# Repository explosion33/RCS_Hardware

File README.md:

# RCS_Hardware
SARP 2023 RCS Flight Controller KiCAD project

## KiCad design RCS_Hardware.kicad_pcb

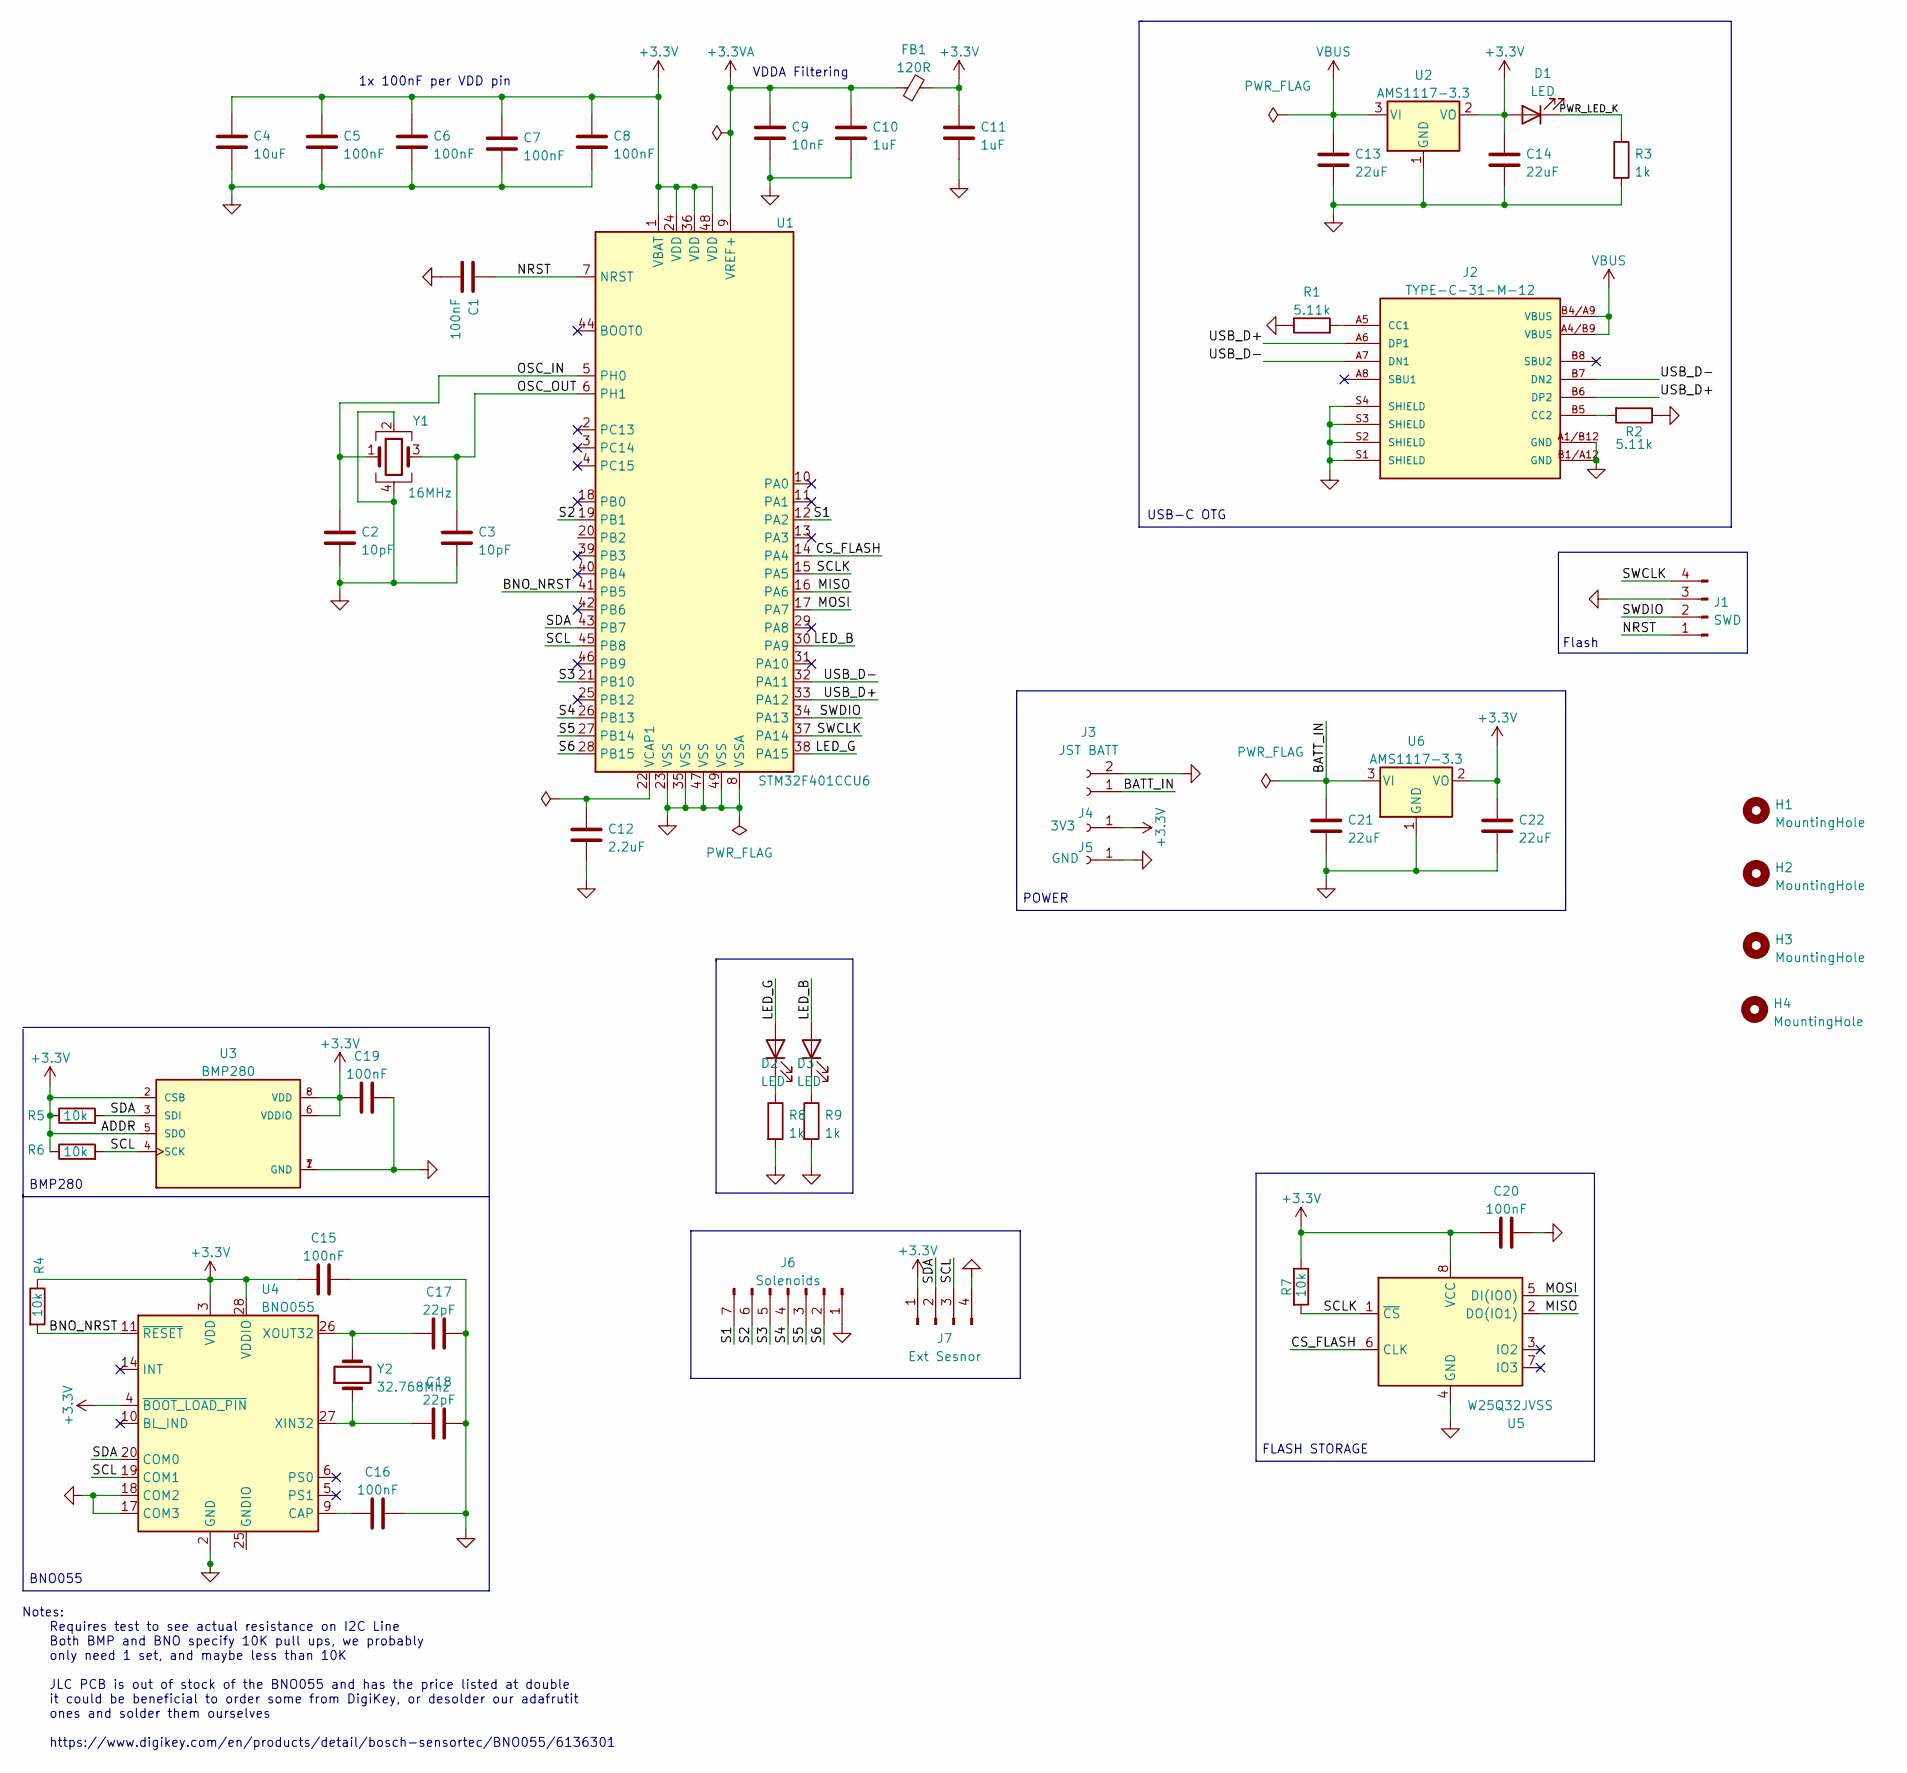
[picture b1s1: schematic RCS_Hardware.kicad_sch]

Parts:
C1, C5, C6, C7, C8, C15, C16, C19, C20: 100nF; C_0402_1005Metric; JLCPCB# C307331
C2, C3: 10pF; C_0402_1005Metric; JLCPCB# C32949
C4: 10uF; C_0603_1608Metric; JLCPCB# C19702
C9: 10nF; C_0402_1005Metric; JLCPCB# C15195
C10, C11: 1uF; C_0402_1005Metric; JLCPCB# C52923
C12: 2.2uF; C_0402_1005Metric; JLCPCB# C12530
C13, C14, C21, C22: 22uF; C_0805_2012Metric; JLCPCB# C5674
C17, C18: 22pF; C_0402_1005Metric; JLCPCB# C466226
D1, D2, D3: LED; LED_0603_1608Metric; JLCPCB# C273598
FB1: 120R; L_0603_1608Metric; JLCPCB# C85831
H1, H2, H3, H4: MountingHole; MountingHole_3.2mm_M3
J1: SWD; PinHeader_1x04_P2.54mm_Vertical
J2: TYPE-C-31-M-12; HRO_TYPE-C-31-M-12; PARTREV 2020.12.08; JLCPCB# C165948
J3: JST BATT; JST_EH_B2B-EH-A_1x02_P2.50mm_Vertical
J4: 3V3; TestPoint_THTPad_2.5x2.5mm_Drill1.2mm
J5: GND; TestPoint_THTPad_2.5x2.5mm_Drill1.2mm
J6: Solenoids; PinHeader_1x07_P2.54mm_Vertical
J7: Ext Sesnor; PinHeader_1x04_P2.54mm_Vertical
R1, R2: 5.11k; R_0402_1005Metric; JLCPCB# C25906
R3, R8, R9: 1k; R_0402_1005Metric; JLCPCB# C11702
R4, R5, R6, R7: 10k; R_0402_1005Metric; JLCPCB# C60490
U1: STM32F401CCU6; QFN-48-1EP_7x7mm_P0.5mm_EP5.6x5.6mm; JLCPCB# C79861
U2, U6: AMS1117-3.3; SOT-223-3_TabPin2; JLCPCB# C6186
U3: BMP280; XDCR_BMP280; PART_REV 1.19; JLCPCB# C83291
U4: BNO055; LGA-28_5.2x3.8mm_P0.5mm; JLCPCB# C93216
U5: W25Q32JVSS; SOIC-8_5.23x5.23mm_P1.27mm; JLCPCB# C82344
Y1: 16MHz; Crystal_SMD_3225-4Pin_3.2x2.5mm; JLCPCB# C13738
Y2: 32.768Mhz; Crystal_SMD_3215-2Pin_3.2x1.5mm; JLCPCB# C907540

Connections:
+3.3V: C4.1, C5.1, C6.1, C7.1, C8.1, C11.1, C14.1, C15.1, C19.2, C20.1, C22.1, D1.2 (A), FB1.2, J4.1, J7.1, R4.1, R5.1, R6.1, R7.1, U1.1 (VBAT), U1.24 (VDD), U1.36 (VDD), U1.48 (VDD), U2.2 (VO), U3.2 (CSB), U3.5 (SDO), U3.6 (VDDIO), U3.8 (VDD), U4.3 (VDD), U4.4 (~BOOT_LOAD_PIN), U4.28 (VDDIO), U5.8 (VCC), U6.2 (VO)
+3.3VA: C9.1, C10.1, FB1.1, U1.9 (VREF+)
/BATT_IN: C21.1, J3.1, U6.3 (VI)
/BNO_NRST: R4.2, U1.41 (PB5), U4.11 (~RESET)
/CS_FLASH: U1.14 (PA4), U5.6 (CLK)
/LED_B: D3.2 (A), U1.30 (PA9)
/LED_G: D2.2 (A), U1.38 (PA15)
/MISO: U1.16 (PA6), U5.2 (DO(IO1))
/MOSI: U1.17 (PA7), U5.5 (DI(IO0))
/NRST: C1.1, J1.1, U1.7 (NRST)
/OSC_IN: C2.1, U1.5 (PH0), Y1.1
/OSC_OUT: C3.1, U1.6 (PH1), Y1.3
/PWR_LED_K: D1.1 (K), R3.1
/S1: J6.7, U1.12 (PA2)
/S2: J6.6, U1.19 (PB1)
/S3: J6.5, U1.21 (PB10)
/S4: J6.4, U1.26 (PB13)
/S5: J6.3, U1.27 (PB14)
/S6: J6.2, U1.28 (PB15)
/SCL: J7.3, R6.2, U1.45 (PB8), U3.4 (SCK), U4.19 (COM1)
/SCLK: R7.2, U1.15 (PA5), U5.1 (~CS)
/SDA: J7.2, R5.2, U1.43 (PB7), U3.3 (SDI), U4.20 (COM0)
/SWCLK: J1.4, U1.37 (PA14)
/SWDIO: J1.2, U1.34 (PA13)
/USB_D+: J2.A6 (DP1), J2.B6 (DP2), U1.33 (PA12)
/USB_D-: J2.A7 (DN1), J2.B7 (DN2), U1.32 (PA11)
GND: C1.2, C2.2, C3.2, C4.2, C5.2, C6.2, C7.2, C8.2, C9.2, C10.2, C11.2, C12.2, C13.2, C14.2, C15.2, C16.2, C17.2, C18.2, C19.1, C20.2, C21.2, C22.2, J1.3, J2.A1/B12 (GND), J2.B1/A12 (GND), J2.S1 (SHIELD), J2.S2 (SHIELD), J2.S3 (SHIELD), J2.S4 (SHIELD), J3.2, J5.1, J6.1, J7.4, R1.1, R2.1, R3.2, R8.2, R9.2, U1.8 (VSSA), U1.23 (VSS), U1.35 (VSS), U1.47 (VSS), U1.49 (VSS), U2.1 (GND), U3.1 (GND), U3.7 (GND), U4.2 (GND), U4.17 (COM3), U4.18 (COM2), U5.4 (GND), U6.1 (GND), Y1.2, Y1.4
unnamed: C12.1, U1.22 (VCAP1)
unnamed: C16.1, U4.9 (CAP)
unnamed: C17.1, U4.26 (XOUT32), Y2.2
unnamed: C18.1, U4.27 (XIN32), Y2.1
unnamed: D2.1 (K), R8.1
unnamed: D3.1 (K), R9.1
unnamed: J2.A5 (CC1), R1.2
unnamed: J2.B5 (CC2), R2.2
unnamed: U4.15 (GNDIO), U4.16 (GNDIO), U4.25 (GNDIO)
VBUS: C13.1, J2.A4/B9 (VBUS), J2.B4/A9 (VBUS), U2.3 (VI)

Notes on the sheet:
VDDA Filtering
Flash
FLASH STORAGE
1x 100nF per VDD pin
Notes: Requires test to see actual resistance on I2C Line Both BMP and BNO specify 10K pull ups, we probably only need 1 set, and maybe less than 10K JLC PCB is out of stock of the BNO055 and has the price listed at double it could be beneficial to order some from DigiKey, or desolder our adafrutit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
USB-C OTG
BNO055
BMP280
POWER

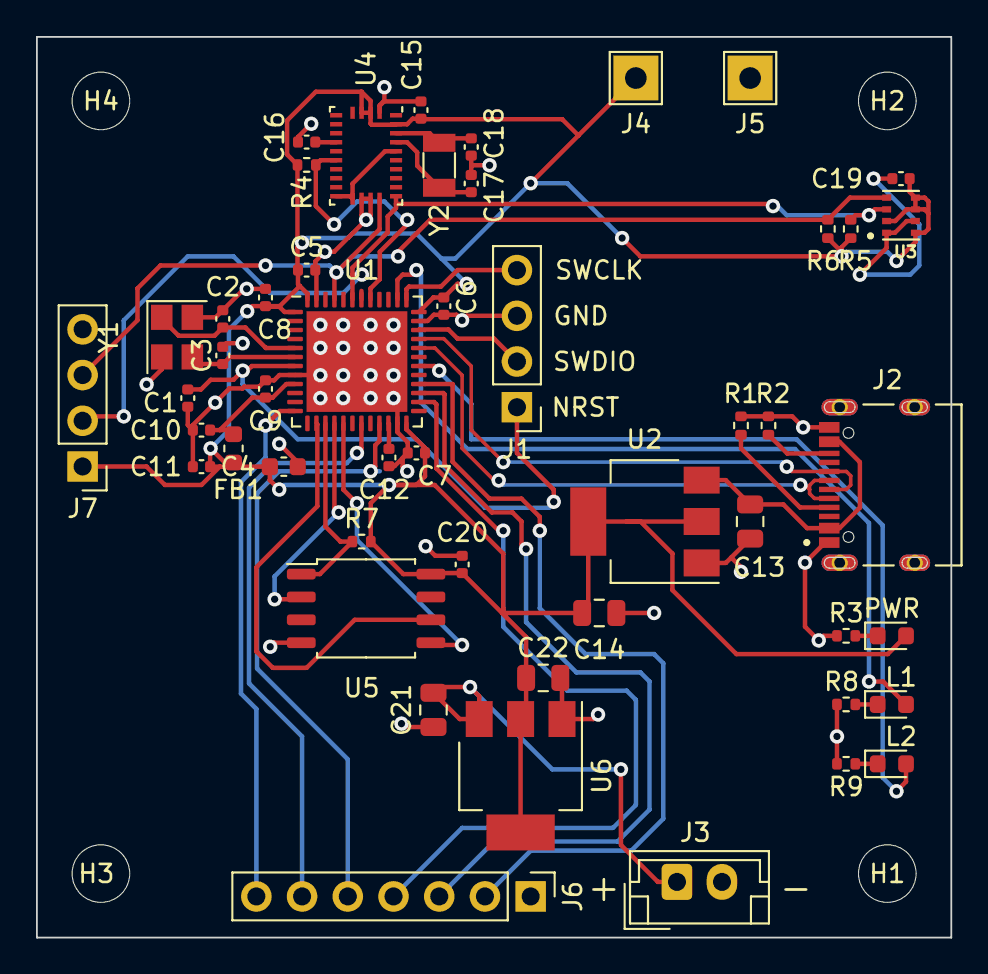
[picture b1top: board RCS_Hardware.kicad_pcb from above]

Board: 2 copper layers, 50.8 x 50.0 mm, 54 parts (0 on the bottom side), 37 nets.

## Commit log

2023-07-08 inital KiCad setup
2023-07-08 forked base stm32f401 and usb-c setup
2023-07-08 added missing USBC foorprint, symbol, and model fixed minor schematic erros setup basic layout for stm32 and capacitors
2023-07-08 added BMP280 files, schematic, and layout added BNO055 files, schematic, and layout contains layout changes of previous commit (not 100% sure they got added)
2023-07-08 added gitignore and cleaned up unescesary project files
2023-07-08 added SPI NOR flash chip fixed minor issues with BNO055 schema completed a rough layout of the entire current pcb
2023-07-10 Added External Power Support Added layout for external Power Updated SilkScreen Fixed Mounting hole layout Added render of board
2023-07-11 added solenoid control pins added external sensor pins added green and blue status leds updated render
2023-07-11 created symbol and footprint for differential driver added schema for diff driver layed out diff driver and connector updated render
